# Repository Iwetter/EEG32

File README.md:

# EEG32

**A 32-channel EEG acquisition board design in KiCad.**

An electronics design project using four ADS1299 analog front ends and an nRF52832 acquisition controller, with shared reference, separate bias, passive inputs, and documented connector/assembly interfaces.

## Project status

The repository captures the `2.1-prefab-bench` design checkpoint dated October 1, 2026. It contains editable schematics and PCB layout, component libraries, a BOM, and pre-fabrication engineering documentation. Fabrication, bench performance, and human-connected use have not been validated. The design documentation retains the outstanding manufacturing and safety review holds.

## Engineering focus

- Multi-channel analog acquisition and MCU interfaces.
- Hierarchical schematic organization and a routed PCB.
- Footprint/library management and component procurement documentation.
- Connector orientation, assembly centroids, and pre-fabrication checks.
- Explicit separation of electrical-rule results from physical qualification.

## Explore the design

| File or directory | Contents |
|---|---|
| [`EEG32.kicad_pro`](EEG32.kicad_pro) | KiCad project entry point |
| [`EEG32.kicad_sch`](EEG32.kicad_sch) | Root schematic and hierarchical sheets |
| [`EEG32.kicad_pcb`](EEG32.kicad_pcb) | PCB layout |
| [`EEG32.pretty/`](EEG32.pretty/) | Project footprints |
| [`BOM.csv`](BOM.csv) | Bill of materials |
| [`prefab-20261001/`](prefab-20261001/) | Release notes, assembly details, qualification, and bench plans |
| [`ERC.json`](ERC.json), [`DRC.json`](DRC.json) | Saved design-check outputs |

Open `EEG32.kicad_pro` with KiCad 10 and keep the repository's relative libraries together. Review [the release report](prefab-20261001/RELEASE-REPORT.md), [bench-validation plan](prefab-20261001/BENCH-VALIDATION.md), and [safety-review inputs](prefab-20261001/SAFETY-REVIEW-INPUTS.md) before interpreting the saved check results.

The source edition excludes historical checkpoints, duplicated archives, machine-local settings, and downloaded vendor documents. References in historical qualification notes may point to files from the original development package.

**Tools:** KiCad · PCB layout · ADS1299 · nRF52832 · ERC/DRC

[Ian Hall's engineering portfolio](https://github.com/Iwetter)

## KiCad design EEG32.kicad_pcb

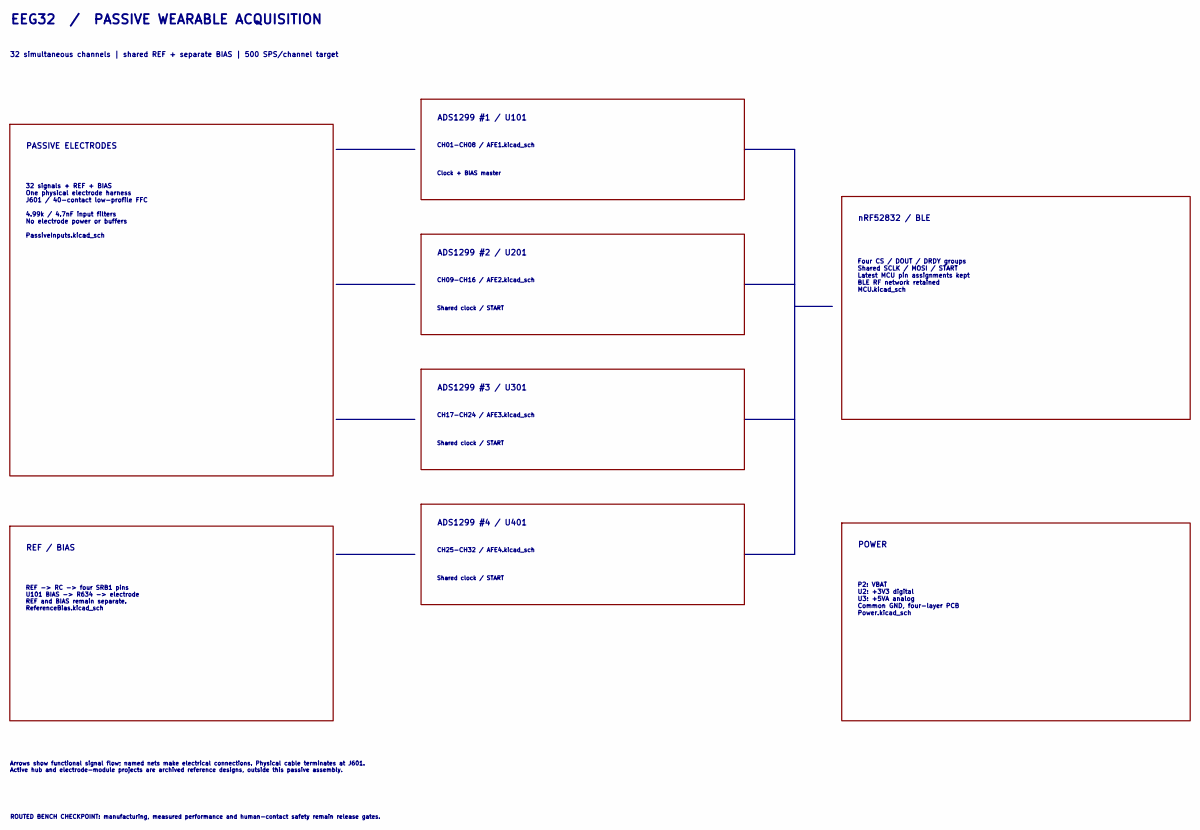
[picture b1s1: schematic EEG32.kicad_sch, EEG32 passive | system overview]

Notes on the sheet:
ADS1299 #4 / U401
CH25-CH32 / AFE4.kicad_sch
Shared clock / START
ADS1299 #2 / U201
CH09-CH16 / AFE2.kicad_sch
ADS1299 #3 / U301
CH17-CH24 / AFE3.kicad_sch
ADS1299 #1 / U101
CH01-CH08 / AFE1.kicad_sch
Clock + BIAS master
EEG32 / PASSIVE WEARABLE ACQUISITION
32 simultaneous channels | shared REF + separate BIAS | 500 SPS/channel target
PASSIVE ELECTRODES
32 signals + REF + BIAS One physical electrode harness J601 / 40-contact low-profile FFC 4.99k / 4.7nF input filters No electrode power or buffers PassiveInputs.kicad_sch
REF / BIAS
REF -> RC -> four SRB1 pins U101 BIAS -> R634 -> electrode REF and BIAS remain separate. ReferenceBias.kicad_sch
nRF52832 / BLE
Four CS / DOUT / DRDY groups Shared SCLK / MOSI / START Latest MCU pin assignments kept BLE RF network retained MCU.kicad_sch
POWER
P2: VBAT U2: +3V3 digital U3: +5VA analog Common GND, four-layer PCB Power.kicad_sch
Arrows show functional signal flow; named nets make electrical connections. Physical cable terminates at J601. Active hub and electrode-module projects are archived reference designs, outside this passive assembly.
ROUTED BENCH CHECKPOINT: manufacturing, measured performance and human-contact safety remain release gates.

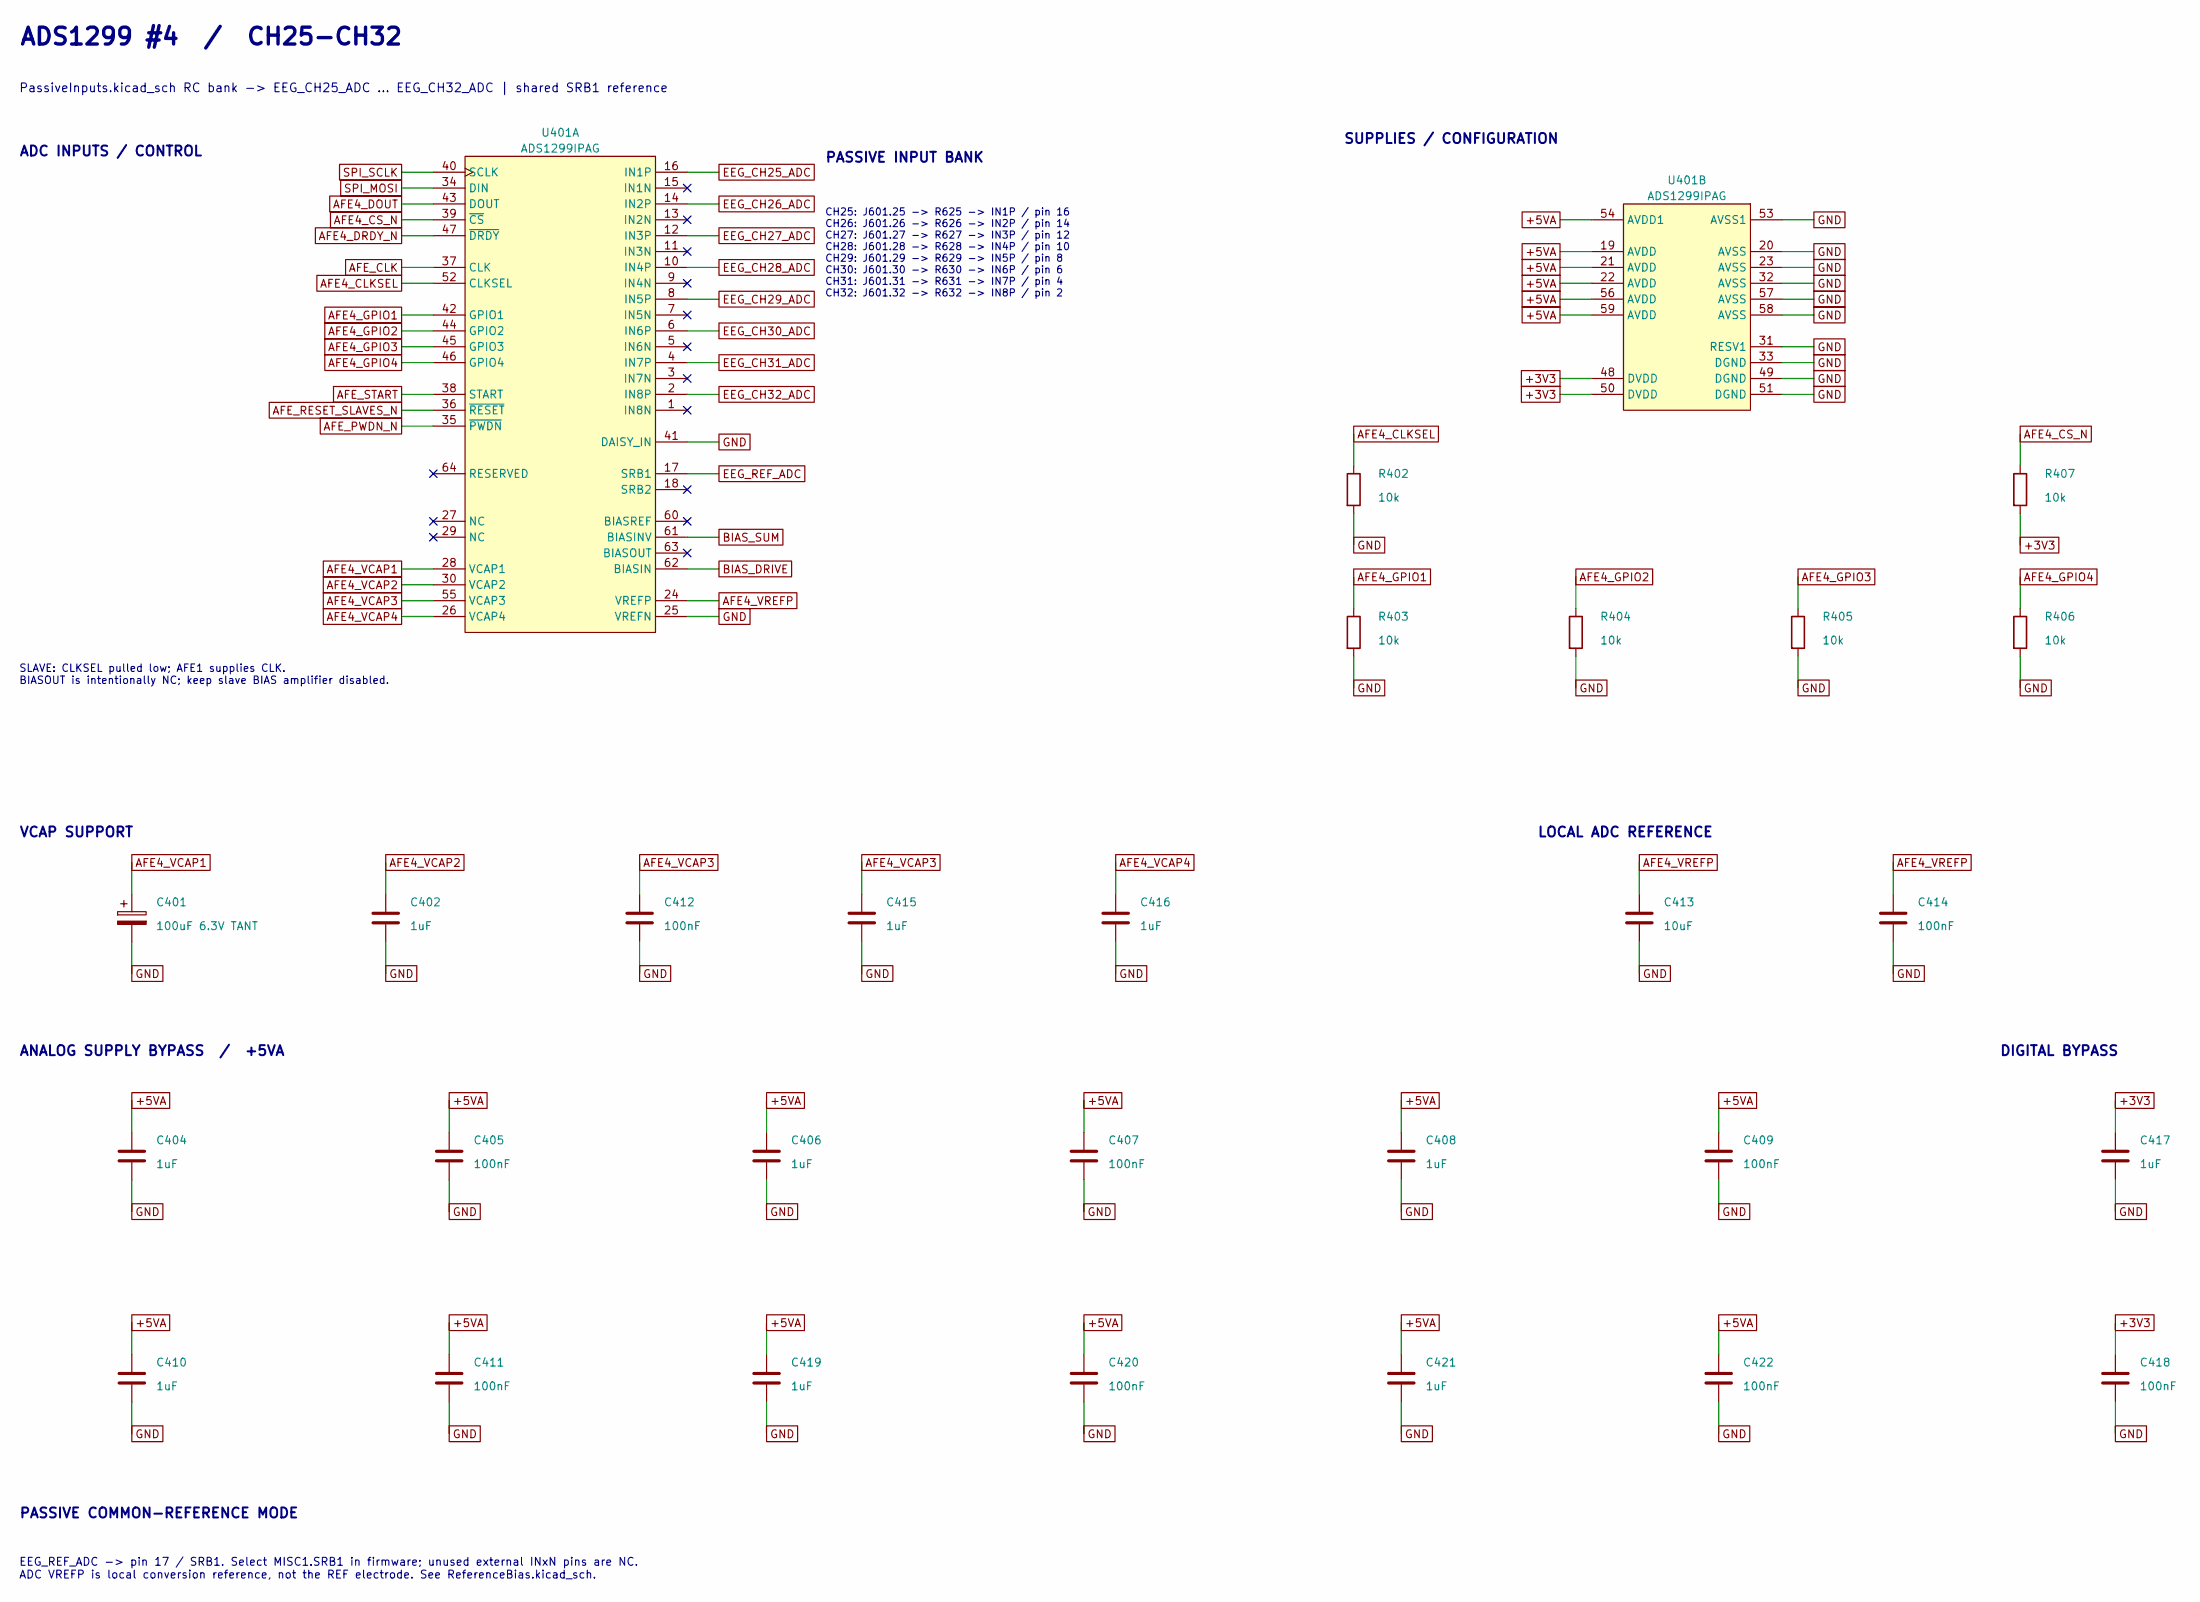
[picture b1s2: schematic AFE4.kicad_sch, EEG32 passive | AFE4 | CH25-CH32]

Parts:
C401: 100uF 6.3V TANT; CP_EIA-3528-21_Kemet-B; MPN T491B107K006AT
C402, C404, C406, C408, C410, C415, C416, C417, C419, C421: 1uF; C0402; MPN GRM155R61A105KE15D
C405, C407, C409, C411, C412, C414, C418, C420, C422: 100nF; C0402; MPN GRM155R71C104KA88D
C413: 10uF; C0603; MPN GRM188R61A106KE69D
R402, R403, R404, R405, R406, R407: 10k; R0402; MPN RC0402FR-0710KL
U401: ADS1299IPAG; PAG0064A_L; MPN ADS1299IPAG

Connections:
+3V3: C417.2, C418.1, R407.2, U401.48 (DVDD), U401.50 (DVDD); also elsewhere on the board
+5VA: C404.1, C405.2, C406.1, C407.2, C408.1, C409.2, C410.1, C411.2, C419.1, C420.1, C421.1, C422.1, U401.19 (AVDD), U401.21 (AVDD), U401.22 (AVDD), U401.54 (AVDD1), U401.56 (AVDD), U401.59 (AVDD); also elsewhere on the board
AFE4_CLKSEL: R402.1, U401.52 (CLKSEL)
AFE4_CS_N: R407.1, U401.39 (~CS); also elsewhere on the board
AFE4_DOUT: U401.43 (DOUT); also elsewhere on the board
AFE4_DRDY_N: U401.47 (~DRDY); also elsewhere on the board
AFE4_GPIO1: R403.1, U401.42 (GPIO1)
AFE4_GPIO2: R404.1, U401.44 (GPIO2)
AFE4_GPIO3: R405.1, U401.45 (GPIO3)
AFE4_GPIO4: R406.1, U401.46 (GPIO4)
AFE4_VCAP1: C401.1, U401.28 (VCAP1)
AFE4_VCAP2: C402.2, U401.30 (VCAP2)
AFE4_VCAP3: C412.2, C415.2, U401.55 (VCAP3)
AFE4_VCAP4: C416.2, U401.26 (VCAP4)
AFE4_VREFP: C413.1, C414.1, U401.24 (VREFP)
AFE_CLK: U401.37 (CLK); also elsewhere on the board
AFE_PWDN_N: U401.35 (~PWDN); also elsewhere on the board
AFE_RESET_SLAVES_N: U401.36 (~RESET); also elsewhere on the board
AFE_START: U401.38 (START); also elsewhere on the board
BIAS_DRIVE: U401.62 (BIASIN); also elsewhere on the board
BIAS_SUM: U401.61 (BIASINV); also elsewhere on the board
EEG_CH25_ADC: U401.16 (IN1P); also elsewhere on the board
EEG_CH26_ADC: U401.14 (IN2P); also elsewhere on the board
EEG_CH27_ADC: U401.12 (IN3P); also elsewhere on the board
EEG_CH28_ADC: U401.10 (IN4P); also elsewhere on the board
EEG_CH29_ADC: U401.8 (IN5P); also elsewhere on the board
EEG_CH30_ADC: U401.6 (IN6P); also elsewhere on the board
EEG_CH31_ADC: U401.4 (IN7P); also elsewhere on the board
EEG_CH32_ADC: U401.2 (IN8P); also elsewhere on the board
EEG_REF_ADC: U401.17 (SRB1); also elsewhere on the board
GND: C401.2, C402.1, C404.2, C405.1, C406.2, C407.1, C408.2, C409.1, C410.2, C411.1, C412.1, C413.2, C414.2, C415.1, C416.1, C417.1, C418.2, C419.2, C420.2, C421.2, C422.2, R402.2, R403.2, R404.2, R405.2, R406.2, U401.20 (AVSS), U401.23 (AVSS), U401.25 (VREFN), U401.31 (RESV1), U401.32 (AVSS), U401.33 (DGND), U401.41 (DAISY_IN), U401.49 (DGND), U401.51 (DGND), U401.53 (AVSS1), U401.57 (AVSS), U401.58 (AVSS); also elsewhere on the board
SPI_MOSI: U401.34 (DIN); also elsewhere on the board
SPI_SCLK: U401.40 (SCLK); also elsewhere on the board

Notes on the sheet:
ADS1299 #4 / CH25-CH32
PassiveInputs.kicad_sch RC bank -> EEG_CH25_ADC ... EEG_CH32_ADC | shared SRB1 reference
ADC INPUTS / CONTROL
SUPPLIES / CONFIGURATION
VCAP SUPPORT
LOCAL ADC REFERENCE
ANALOG SUPPLY BYPASS / +5VA
DIGITAL BYPASS
PASSIVE COMMON-REFERENCE MODE
EEG_REF_ADC -> pin 17 / SRB1. Select MISC1.SRB1 in firmware; unused external INxN pins are NC. ADC VREFP is local conversion reference, not the REF electrode. See ReferenceBias.kicad_sch.
SLAVE: CLKSEL pulled low; AFE1 supplies CLK. BIASOUT is intentionally NC; keep slave BIAS amplifier disabled.
PASSIVE INPUT BANK
CH25: J601.25 -> R625 -> IN1P / pin 16 CH26: J601.26 -> R626 -> IN2P / pin 14 CH27: J601.27 -> R627 -> IN3P / pin 12 CH28: J601.28 -> R628 -> IN4P / pin 10 CH29: J601.29 -> R629 -> IN5P / pin 8 CH30: J601.30 -> R630 -> IN6P / pin 6 CH31: J601.31 -> R631 -> IN7P / pin 4 CH32: J601.32 -> R632 -> IN8P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

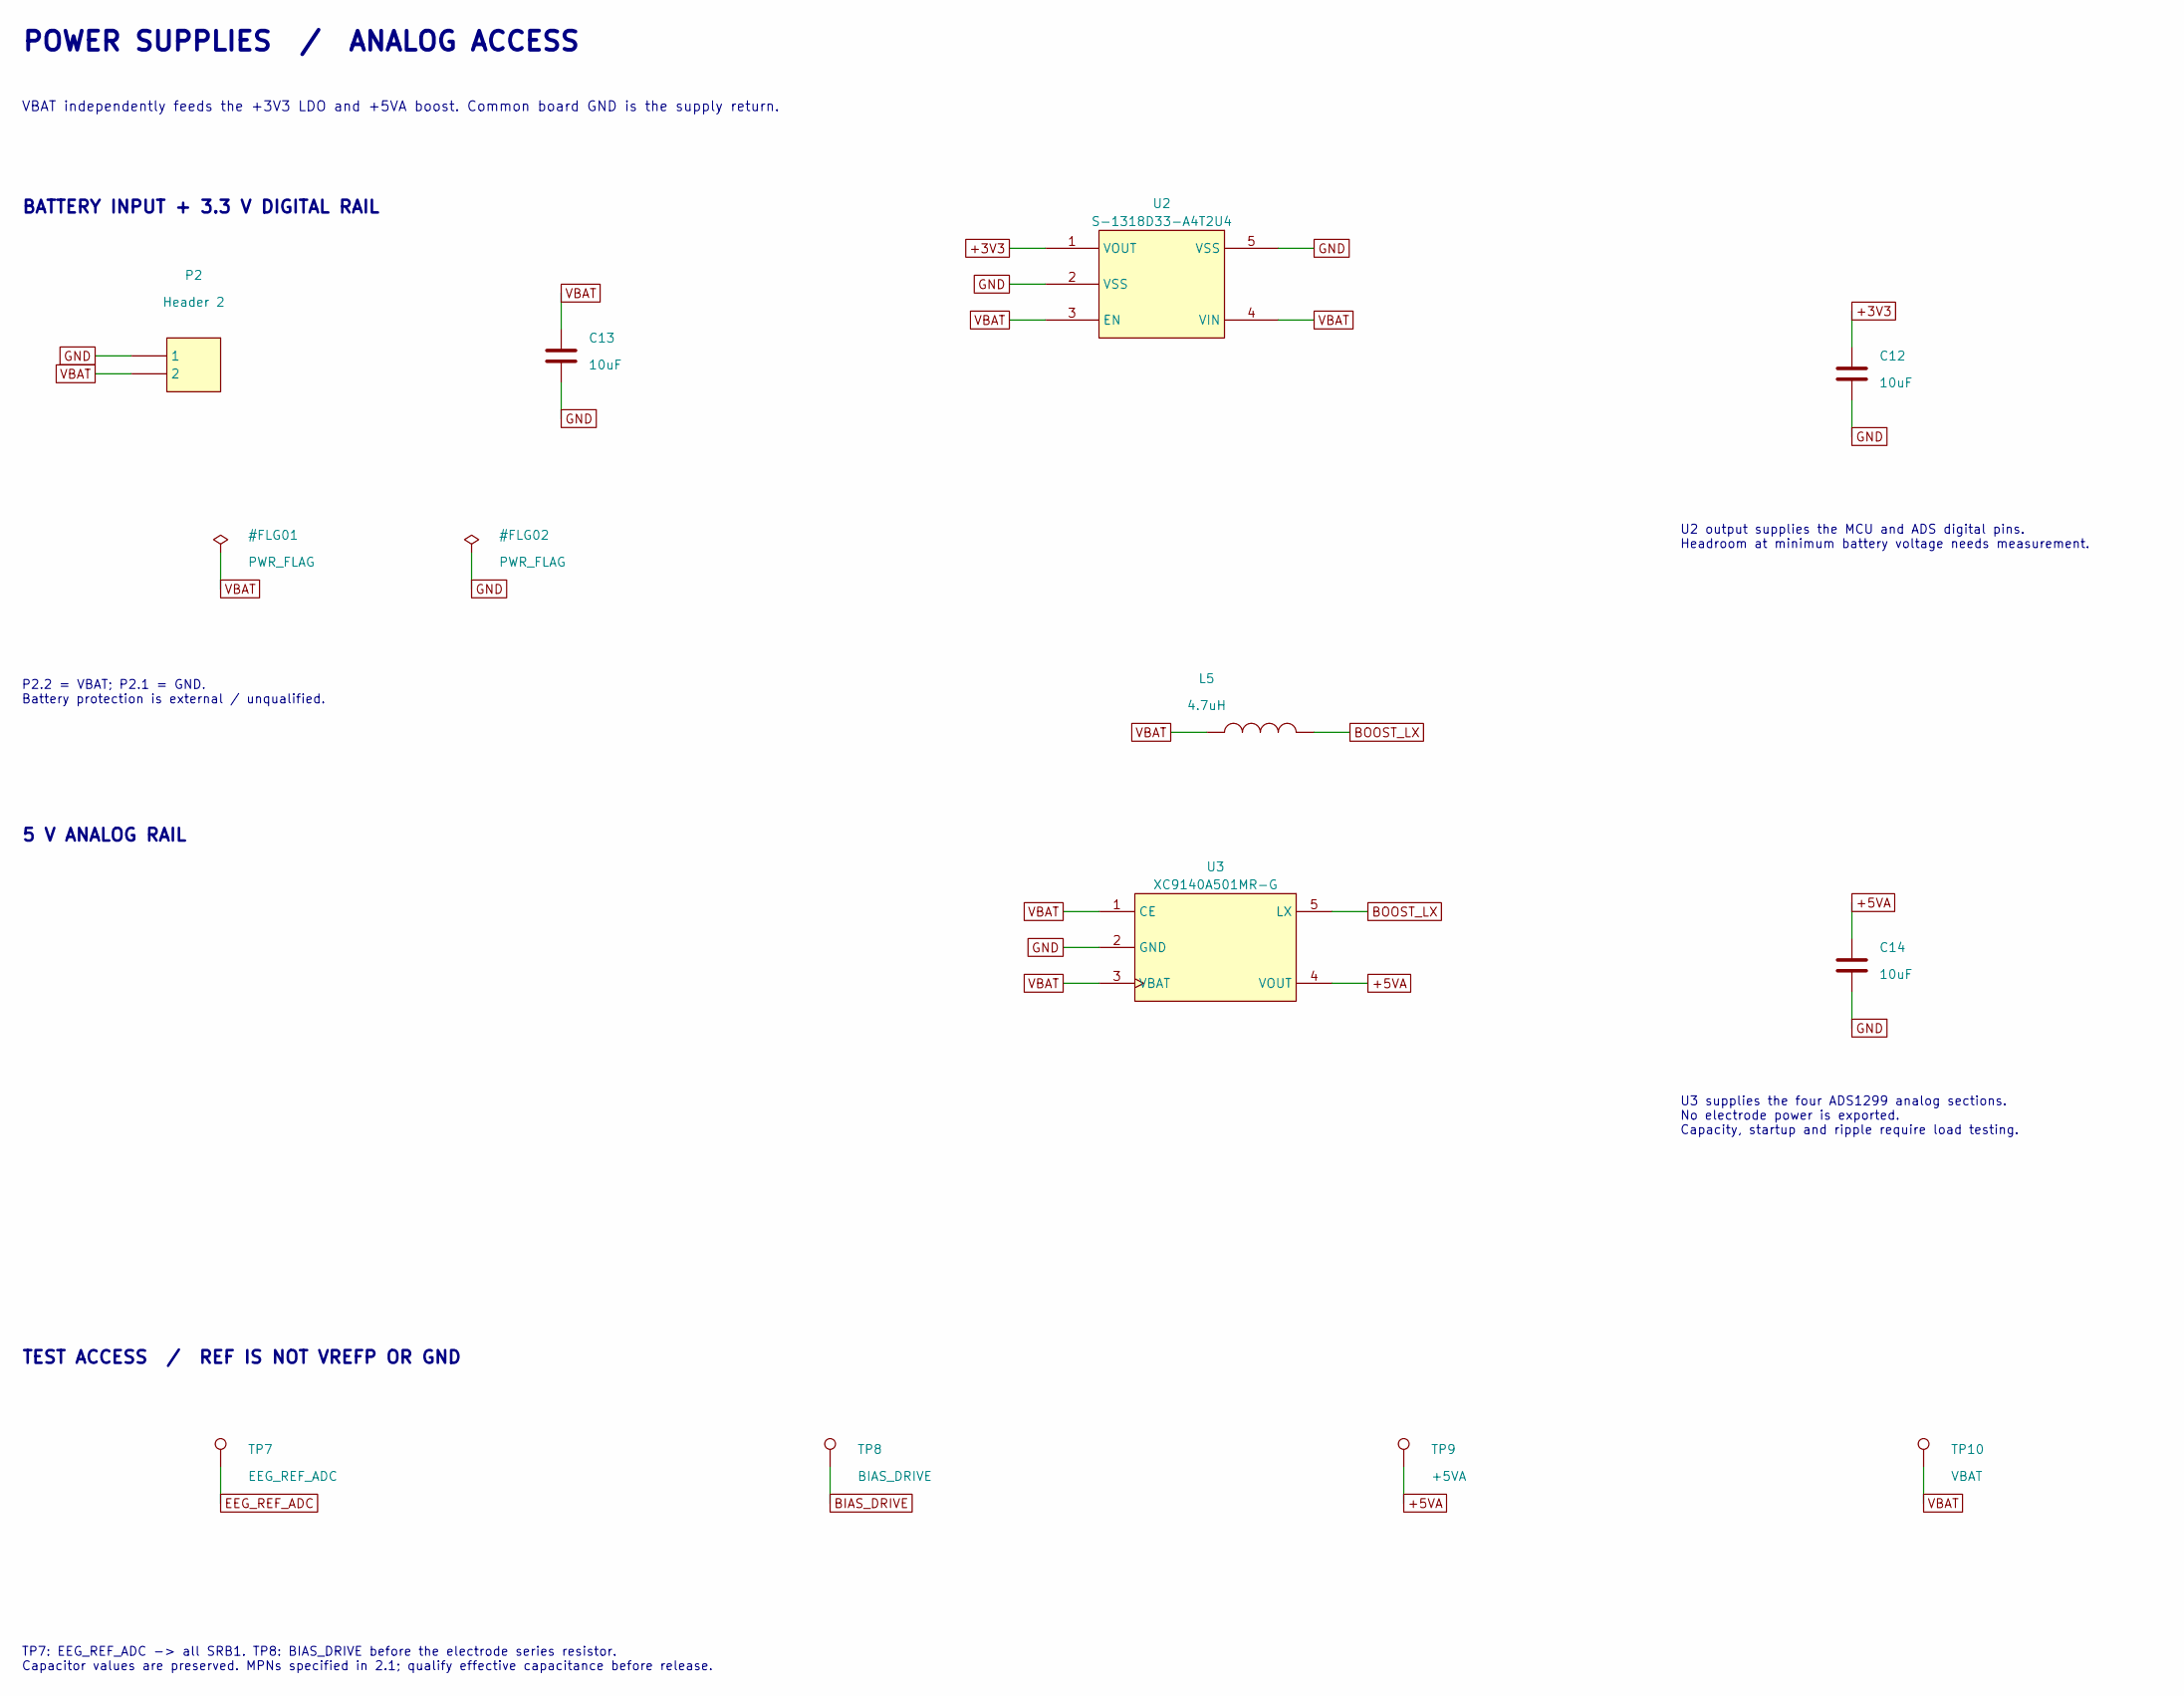
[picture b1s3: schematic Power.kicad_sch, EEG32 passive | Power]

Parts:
C12, C13, C14: 10uF; C0402; MPN GRM155R61A106ME11D
L5: 4.7uH; L0603; MPN LQM18PN4R7MFRL
P2: Header 2; HDR1X2; MPN NOT PURCHASED
TP7: EEG_REF_ADC; TestPoint_Pad_D1.5mm; MPN NOT PURCHASED
TP8: BIAS_DRIVE; TestPoint_Pad_D1.5mm; MPN NOT PURCHASED
TP9: +5VA; TestPoint_Pad_D1.5mm; MPN NOT PURCHASED
TP10: VBAT; TestPoint_Pad_D1.5mm; MPN NOT PURCHASED
U2: S-1318D33-A4T2U4; S-1318_A4T2U4; MPN S-1318D33-A4T2U4
U3: XC9140A501MR-G; FP-DBV0005A-IPC_C; MPN XC9140A501MR-G

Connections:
+3V3: C12.2, U2.1 (VOUT); also elsewhere on the board
+5VA: C14.1, TP9.1, U3.4 (VOUT); also elsewhere on the board
BIAS_DRIVE: TP8.1; also elsewhere on the board
BOOST_LX: L5.2, U3.5 (LX)
EEG_REF_ADC: TP7.1; also elsewhere on the board
GND: C12.1, C13.2, C14.2, P2.1, U2.2 (VSS), U2.5 (VSS), U3.2 (GND); also elsewhere on the board
VBAT: C13.1, L5.1, P2.2, TP10.1, U2.3 (EN), U2.4 (VIN), U3.1 (CE), U3.3 (VBAT)

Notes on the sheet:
POWER SUPPLIES / ANALOG ACCESS
VBAT independently feeds the +3V3 LDO and +5VA boost. Common board GND is the supply return.
BATTERY INPUT + 3.3 V DIGITAL RAIL
P2.2 = VBAT; P2.1 = GND. Battery protection is external / unqualified.
5 V ANALOG RAIL
U2 output supplies the MCU and ADS digital pins. Headroom at minimum battery voltage needs measurement.
U3 supplies the four ADS1299 analog sections. No electrode power is exported. Capacity, startup and ripple require load testing.
TEST ACCESS / REF IS NOT VREFP OR GND
TP7: EEG_REF_ADC -> all SRB1. TP8: BIAS_DRIVE before the electrode series resistor. Capacitor values are preserved. MPNs specified in 2.1; qualify effective capacitance before release.

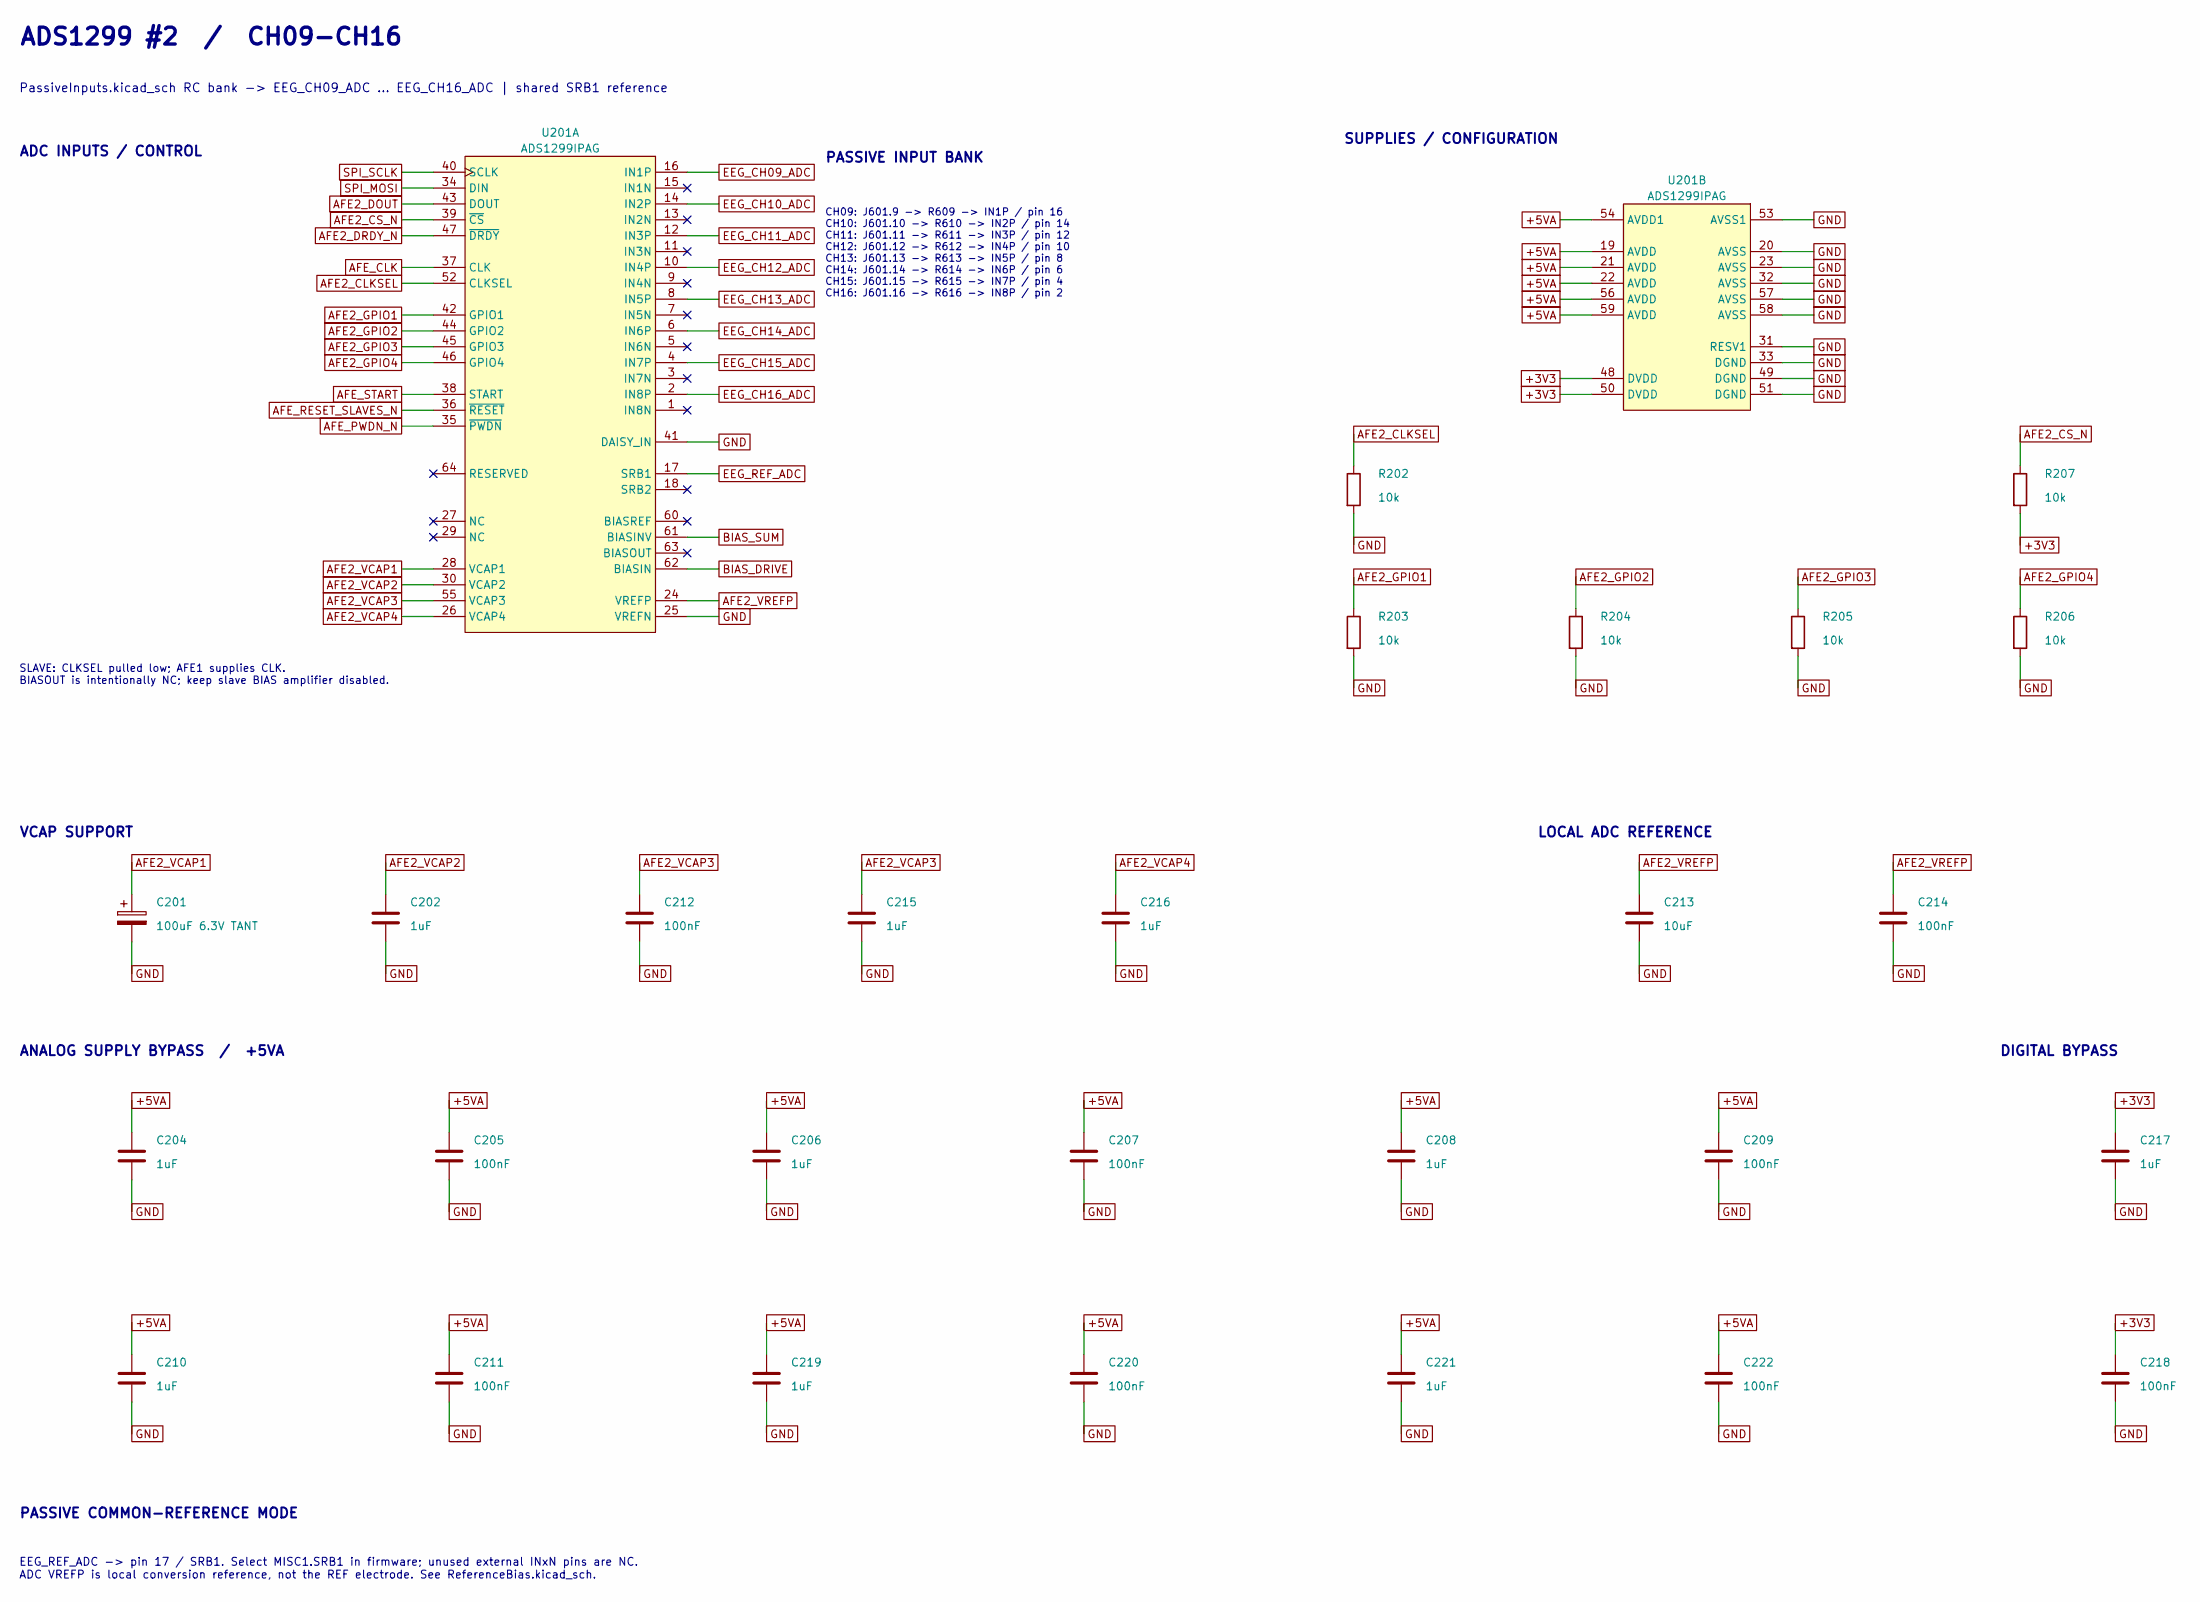
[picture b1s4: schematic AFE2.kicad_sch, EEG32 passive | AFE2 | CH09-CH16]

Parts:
C201: 100uF 6.3V TANT; CP_EIA-3528-21_Kemet-B; MPN T491B107K006AT
C202, C204, C206, C208, C210, C215, C216, C217, C219, C221: 1uF; C0402; MPN GRM155R61A105KE15D
C205, C207, C209, C211, C212, C214, C218, C220, C222: 100nF; C0402; MPN GRM155R71C104KA88D
C213: 10uF; C0603; MPN GRM188R61A106KE69D
R202, R203, R204, R205, R206, R207: 10k; R0402; MPN RC0402FR-0710KL
U201: ADS1299IPAG; PAG0064A_L; MPN ADS1299IPAG

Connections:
+3V3: C217.2, C218.1, R207.2, U201.48 (DVDD), U201.50 (DVDD); also elsewhere on the board
+5VA: C204.1, C205.2, C206.1, C207.2, C208.1, C209.2, C210.1, C211.2, C219.1, C220.1, C221.1, C222.1, U201.19 (AVDD), U201.21 (AVDD), U201.22 (AVDD), U201.54 (AVDD1), U201.56 (AVDD), U201.59 (AVDD); also elsewhere on the board
AFE2_CLKSEL: R202.1, U201.52 (CLKSEL)
AFE2_CS_N: R207.1, U201.39 (~CS); also elsewhere on the board
AFE2_DOUT: U201.43 (DOUT); also elsewhere on the board
AFE2_DRDY_N: U201.47 (~DRDY); also elsewhere on the board
AFE2_GPIO1: R203.1, U201.42 (GPIO1)
AFE2_GPIO2: R204.1, U201.44 (GPIO2)
AFE2_GPIO3: R205.1, U201.45 (GPIO3)
AFE2_GPIO4: R206.1, U201.46 (GPIO4)
AFE2_VCAP1: C201.1, U201.28 (VCAP1)
AFE2_VCAP2: C202.2, U201.30 (VCAP2)
AFE2_VCAP3: C212.2, C215.2, U201.55 (VCAP3)
AFE2_VCAP4: C216.2, U201.26 (VCAP4)
AFE2_VREFP: C213.1, C214.1, U201.24 (VREFP)
AFE_CLK: U201.37 (CLK); also elsewhere on the board
AFE_PWDN_N: U201.35 (~PWDN); also elsewhere on the board
AFE_RESET_SLAVES_N: U201.36 (~RESET); also elsewhere on the board
AFE_START: U201.38 (START); also elsewhere on the board
BIAS_DRIVE: U201.62 (BIASIN); also elsewhere on the board
BIAS_SUM: U201.61 (BIASINV); also elsewhere on the board
EEG_CH09_ADC: U201.16 (IN1P); also elsewhere on the board
EEG_CH10_ADC: U201.14 (IN2P); also elsewhere on the board
EEG_CH11_ADC: U201.12 (IN3P); also elsewhere on the board
EEG_CH12_ADC: U201.10 (IN4P); also elsewhere on the board
EEG_CH13_ADC: U201.8 (IN5P); also elsewhere on the board
EEG_CH14_ADC: U201.6 (IN6P); also elsewhere on the board
EEG_CH15_ADC: U201.4 (IN7P); also elsewhere on the board
EEG_CH16_ADC: U201.2 (IN8P); also elsewhere on the board
EEG_REF_ADC: U201.17 (SRB1); also elsewhere on the board
GND: C201.2, C202.1, C204.2, C205.1, C206.2, C207.1, C208.2, C209.1, C210.2, C211.1, C212.1, C213.2, C214.2, C215.1, C216.1, C217.1, C218.2, C219.2, C220.2, C221.2, C222.2, R202.2, R203.2, R204.2, R205.2, R206.2, U201.20 (AVSS), U201.23 (AVSS), U201.25 (VREFN), U201.31 (RESV1), U201.32 (AVSS), U201.33 (DGND), U201.41 (DAISY_IN), U201.49 (DGND), U201.51 (DGND), U201.53 (AVSS1), U201.57 (AVSS), U201.58 (AVSS); also elsewhere on the board
SPI_MOSI: U201.34 (DIN); also elsewhere on the board
SPI_SCLK: U201.40 (SCLK); also elsewhere on the board

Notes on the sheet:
ADS1299 #2 / CH09-CH16
PassiveInputs.kicad_sch RC bank -> EEG_CH09_ADC ... EEG_CH16_ADC | shared SRB1 reference
ADC INPUTS / CONTROL
SUPPLIES / CONFIGURATION
VCAP SUPPORT
LOCAL ADC REFERENCE
ANALOG SUPPLY BYPASS / +5VA
DIGITAL BYPASS
PASSIVE COMMON-REFERENCE MODE
EEG_REF_ADC -> pin 17 / SRB1. Select MISC1.SRB1 in firmware; unused external INxN pins are NC. ADC VREFP is local conversion reference, not the REF electrode. See ReferenceBias.kicad_sch.
SLAVE: CLKSEL pulled low; AFE1 supplies CLK. BIASOUT is intentionally NC; keep slave BIAS amplifier disabled.
PASSIVE INPUT BANK
CH09: J601.9 -> R609 -> IN1P / pin 16 CH10: J601.10 -> R610 -> IN2P / pin 14 CH11: J601.11 -> R611 -> IN3P / pin 12 CH12: J601.12 -> R612 -> IN4P / pin 10 CH13: J601.13 -> R613 -> IN5P / pin 8 CH14: J601.14 -> R614 -> IN6P / pin 6 CH15: J601.15 -> R615 -> IN7P / pin 4 CH16: J601.16 -> R616 -> IN8P 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
